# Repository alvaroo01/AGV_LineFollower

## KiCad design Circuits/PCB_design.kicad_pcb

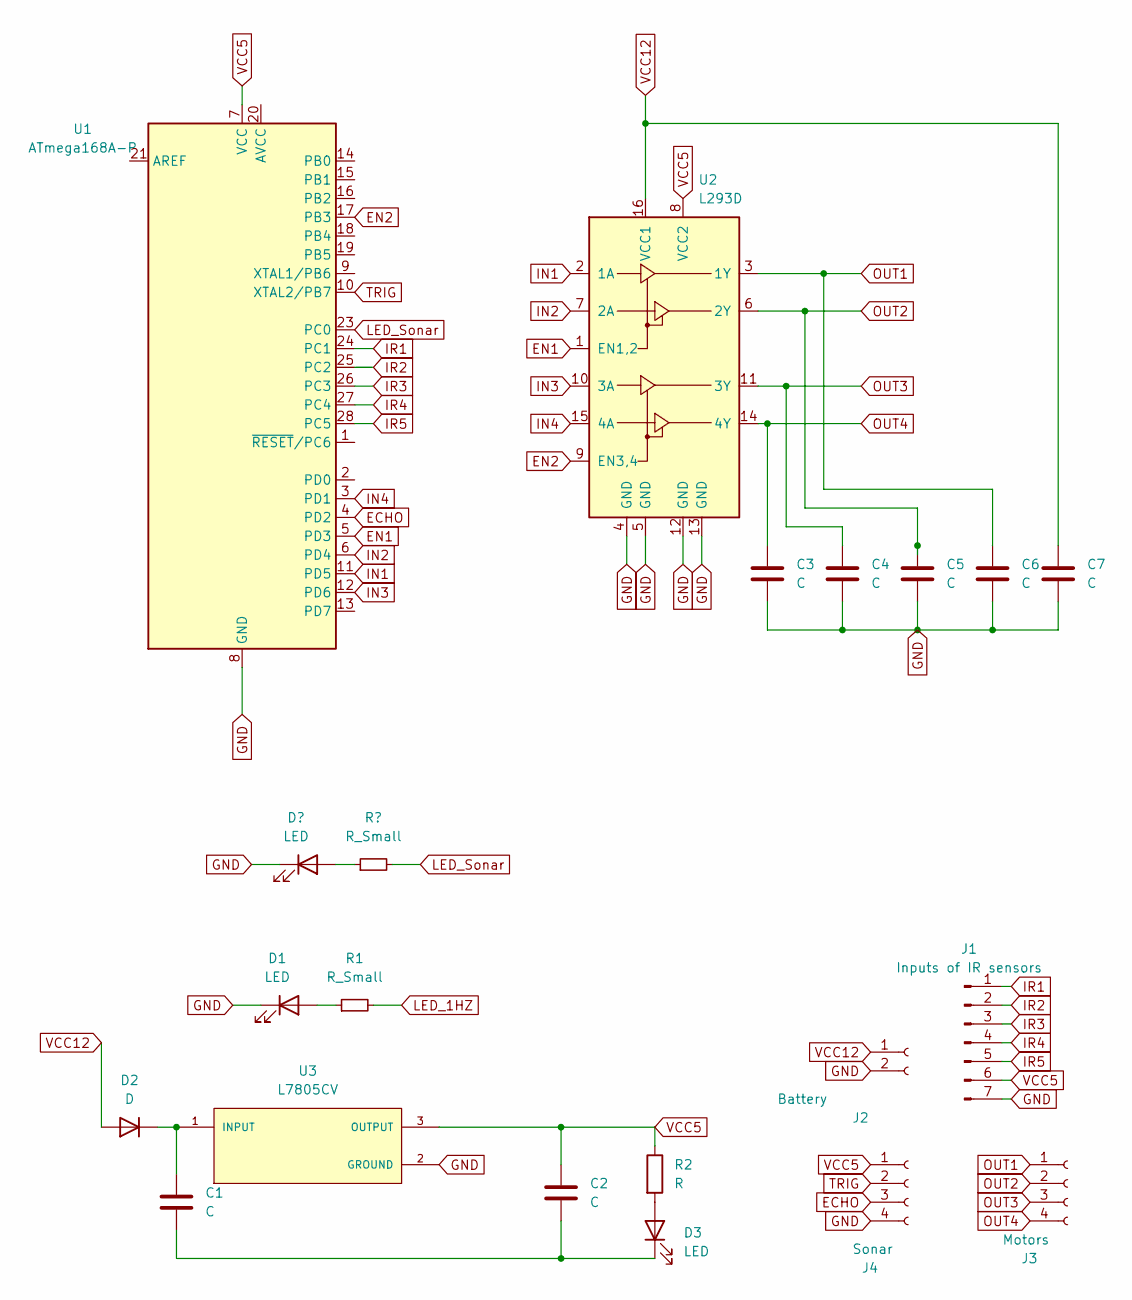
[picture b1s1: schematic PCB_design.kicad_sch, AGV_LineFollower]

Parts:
C1, C2, C3, C4, C5, C6, C7: C; C_Disc_D4.3mm_W1.9mm_P5.00mm
D1, D3: LED; LED_D3.0mm
D2: D; D_5W_P12.70mm_Horizontal
J1: Inputs of IR sensors; PinHeader_1x07_P2.54mm_Vertical
J2: Battery; PinSocket_1x02_P2.54mm_Vertical
J3: Motors; PinSocket_1x04_P2.54mm_Vertical
J4: Sonar; PinSocket_1x04_P2.54mm_Vertical
R1: R_Small; RESAD700W45L350D185
R2: R; RESAD700W45L350D185
U1: ATmega168A-P; DIP-28_W7.62mm
U2: L293D; DIP-16_W7.62mm
U3: L7805CV; TO255P1040X460X1968-3; PARTREV 36

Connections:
ECHO: J4.3, U1.4 (PD2)
EN1: U1.5 (PD3), U2.1 (EN1,2)
EN2: U1.17 (PB3), U2.9 (EN3,4)
GND: C3.2, C4.2, C5.2, C6.2, C7.2, D1.1 (K), J1.7, J2.2, J4.4, U1.8 (GND), U1.22 (GND), U2.4 (GND), U2.5 (GND), U2.12 (GND), U2.13 (GND), U3.2 (GROUND)
IN1: U1.11 (PD5), U2.2 (1A)
IN2: U1.6 (PD4), U2.7 (2A)
IN3: U1.12 (PD6), U2.10 (3A)
IN4: U1.3 (PD1), U2.15 (4A)
IR1: J1.1, U1.24 (PC1)
IR2: J1.2, U1.25 (PC2)
IR3: J1.3, U1.26 (PC3)
IR4: J1.4, U1.27 (PC4)
IR5: J1.5, U1.28 (PC5)
LED_1HZ: R1.2, U1.9 (XTAL1/PB6)
unnamed: C1.1, D2.1 (K), U3.1 (INPUT)
unnamed: C1.2, C2.2, D3.1 (K)
unnamed: D1.2 (A), R1.1
unnamed: D3.2 (A), R2.2
OUT1: C6.1, J3.1, U2.3 (1Y)
OUT2: C5.1, J3.2, U2.6 (2Y)
OUT3: C4.1, J3.3, U2.11 (3Y)
OUT4: C3.1, J3.4, U2.14 (4Y)
TRIG: J4.2, U1.10 (XTAL2/PB7)
VCC5: C2.1, J1.6, J4.1, R2.1, U1.7 (VCC), U2.8 (VCC2), U3.3 (OUTPUT)
VCC12: C7.1, D2.2 (A), J2.1, U2.16 (VCC1)

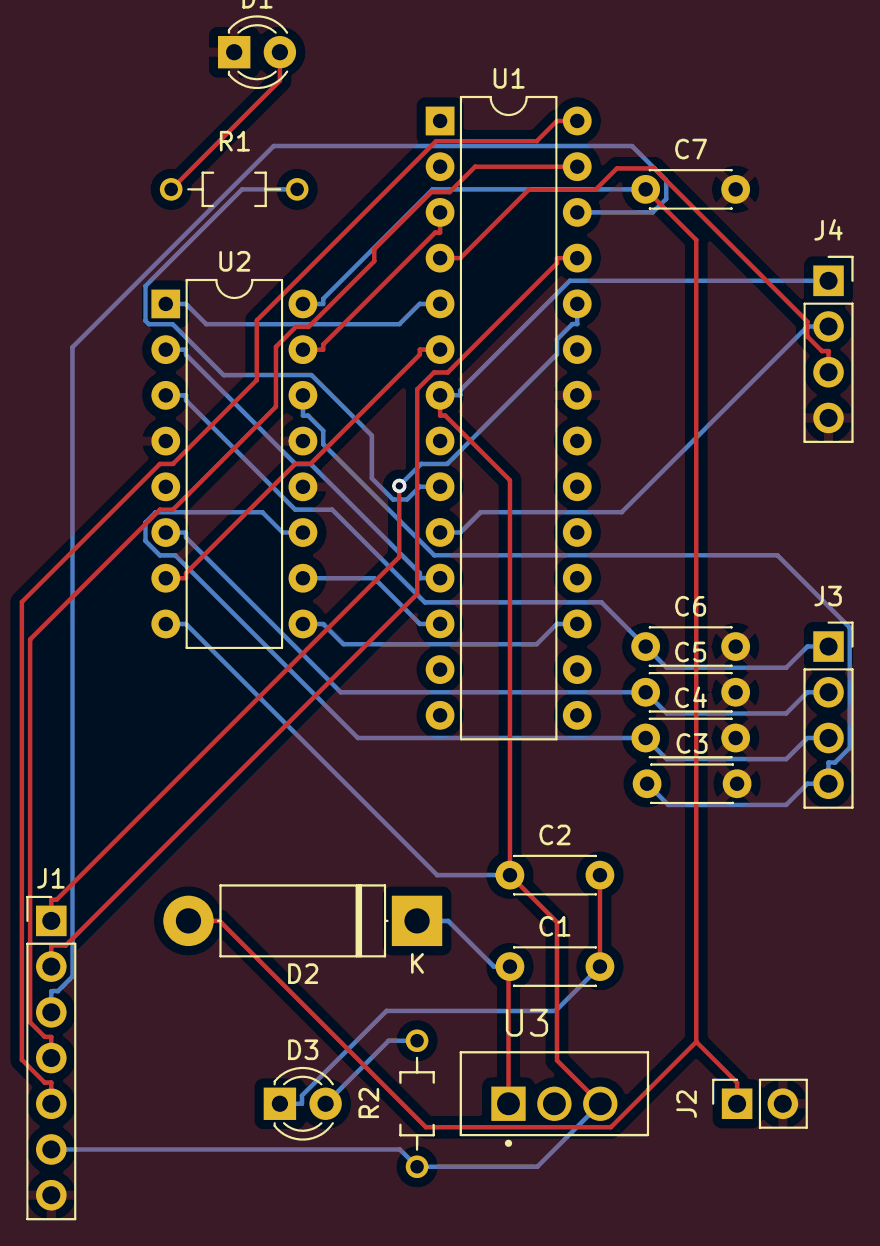
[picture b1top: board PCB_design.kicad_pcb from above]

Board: 2 copper layers, 19 parts (0 on the bottom side), 25 nets.

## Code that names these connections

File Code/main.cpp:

/*
AGV_Linefollower 
Created by:
	Álvaro Lopes-Cardoso
	Fabien Lefebvre
Date: 
	22/01/2022
*/

#include <avr/io.h>									// All the Includes necessary.
#include <stdio.h>
#define F_CPU 1000000UL
#include <util/delay.h>
#include <avr/interrupt.h>

#define motor1_velocity PD3							// Several Defines.
#define motor1_pinA PD5
#define motor1_pinB PD4
#define motor2_velocity PB3
#define motor2_pinA PD6
#define motor2_pinB PD1
#define infra_1 PC0
#define infra_2 PC1
#define infra_3 PC2
#define infra_4 PC3
#define infra_5 PC4
#define led PB2
#define delay_ 5000
#define led_1hZ PB6 
#define test_led PC0
#define Sonar_Led1 PD7
#define Sonar_Trig PB7


typedef struct										// Flag struct.
{
	unsigned char flag_ir1;
	unsigned char flag_ir2;
	unsigned char flag_ir3;
	unsigned char flag_ir4;
	unsigned char flag_ir5;
	unsigned char start_flag;
	unsigned char flag_sonar;

	
} Flags_st;

volatile Flags_st flags={0,0,0,0,0,0};

int cnt = 100;											// Counter for TC0 Interrupt.
int cm;													// Stores the distance measured by the sonar. 
int wave_time;											// Stores the time that the sonar wave took to go from the sonar to the object and back to the sonar
int sonf;												// Sonar flag for interruption. 

void init(void){
														// 0 is input and 1 is output.
														// 1 turns on Led and 0 turns off.
	DDRC = 0b00000000;									// Sets PC1, PC2, PC3, PC4, PC5 as inputs for infrareds. 
	DDRD = 0b11111010;									// Motors outputs (IN's and EN1) and Echo pin for Sonar as input and PD7 as output for Sonar Led.
	DDRB = 0b10001000;									// Motor output (EN2) output for 1Hz blinking led.
	
	PORTD = 0b00000000;									// Clear all the pins on PORTD.
	PORTB = 0b00000101;									
	PORTC = 0b00000000;									// Clears Sonar led to be off by default.
	
	//Making the 1Hz led
	
	TCCR0A = 0b00000010;								// (1<<WGM01) for CTC mode.						
	TCCR0B = 0b00000100;								// (1<<CS02) Prescaler of 256 .
	TIMSK0 = 0b00000010;								// (1<<OCIE0A) Enables Compare match A .
	OCR0A  = 19;										
	
	TCCR1A = 0b00000000;								
	EICRA = 0b00000001;									// (1<<ISC00).
	EIMSK = 0b00000001;								    // (1<<INT0).
	
	TCCR2A = 0b10100011;							    // Clear OC2B and OC2A on compare match and define operation mode as Fast PWM.
	TCCR2B = 0b00000101;								// (1<<CS22) (1<<CS20) Prescaler of 128.
	OCR2B=0;											// Left motor pwm.
	OCR2A=0;											// Right motor pwm.
	
	sei();												// Activates all interruptions.
}


void sonar(void)
{
	PORTB|=(1<<Sonar_Trig);								// Trig pin in set on HIGH.
	_delay_us(10);										// Waits for 10us. 
	PORTB &=~(1<<Sonar_Trig);							// Trig pin in set on LOW.
	cm = (wave_time/58);								// The distance is calculated.		

	if(cm<=25)											// If the distance is less than 25cm then...
	{
		flags.flag_sonar = 1;							// Sonar flag goes to 1.
		PORTD |= (1<<Sonar_Led1);						// Sonar led turns on
		}else{
		PORTD &= ~(1<<Sonar_Led1);						// Sonar led turns off
		flags.flag_sonar = 0;							// Sonar flag goes to 0.
	}
}




void forward (int vel){									// Car goes forward.
	
	OCR2B = vel;										// Sets the speed of both motors
	OCR2A = vel;
	//M1
	PORTD |= (1<<motor1_pinA);							// Current flows in a certain direction allowing both motors to be in the forward direction
	PORTD &= ~(1<<motor1_pinB);
	//M2
	PORTD |= (1<<motor2_pinA);	
	PORTD &= ~(1<<motor2_pinB);
	
}

void backwards (int vel){								// Car goes backwards.
	//M1
	OCR2B = vel;										// Sets the speed of both motors.
	OCR2A = vel;
	PORTD &= ~(1<<motor1_pinA);							// Current flows in a certain direction allowing both motors to be in the backwards direction.
	PORTD |= (1<<motor1_pinB);							
	//M2
	PORTD &= ~(1<<motor2_pinA);
	PORTD |= (1<<motor2_pinB);
	
}

void stop (){											// Car stops.
	//M1
	OCR2B = 0;											// Sets the speed of both motors at 0.
	OCR2A = 0;
	PORTD &= ~(1<<motor1_pinA);							// No current goes to the motors.
	PORTD &= ~(1<<motor1_pinB);
	//M2
	PORTD &= ~(1<<motor2_pinA);
	PORTD &= ~(1<<motor2_pinB);
}

void left (int vel1, int vel2){							// Car goes right (The name of the function relates to the motor thats rotating, so if the left motor is rotating and the right one isn't the car goes right).
	//right motor is A	
	//left motor is B
	OCR2B = vel1;										// Sets the speed of both motors.
	OCR2A = vel2;
	PORTD |= (1<<motor1_pinA);							// Current flows in a certain direction allowing both motors to be in the forward direction.
	PORTD &= ~(1<<motor1_pinB);
}

void right (int vel1, int vel2){						// Car goes left (The name of the function relates to the motor thats rotating, so if the right motor is rotating and the left one isn't the car goes left).
	//right motor is A
	//left motor is B
	OCR2B = vel2;										// Sets the speed of both motors.
	OCR2A = vel1;
	PORTD |= (1<<motor1_pinA);							// Current flows in a certain direction allowing both motors to be in the forward direction.
	PORTD &= ~(1<<motor1_pinB);	
}
	
void start (int start_vel){								// Function that determines when the car starts.
	if ((PINC | 0b11000001) == 0b11000001)				// If every IR Sensor is detecting black then the car starts.	
		{
		forward(start_vel);								// The car starts going forward.
		flags.start_flag = 1;							// Changes the start_flag to 1.
		}
		}

void ir_sensors(	int start_vel, int low_speed){			// Function that determines when the car changes direction or stops when it has already started.
	sonar();												// Runs the sonar() funciton.
	if ((PINC | 0b11111101) == 0b11111101){					// If IR1 is detecting black...
		while(!((PINC | 0b11110111) == 0b11110111)){		// While IR3 isn't detecting black...
			right(start_vel,0);								// Car goes left.
		}		
		
		} else if ((PINC | 0b11011111) == 0b11011111){		// If IR5 is detecting black...
		while(!((PINC | 0b11110111) == 0b11110111)){		// While IR3 isn't detecting black...
			left(start_vel,0);								// Car goes right.
		}
		
		} else if ((PINC | 0b11101111) == 0b11101111){		// If IR4 is detecting black...
			left(start_vel,0);								// Car goes right.
		
		} else if ((PINC | 0b11111011) == 0b11111011){		// If IR2 is detecting black...
			right(start_vel,0);								// Car goes left.
			
		} else if (flags.flag_sonar==1){					// If Sonar detects an object...
			while(!(flags.flag_sonar==0)) {					// While it doesn't stop detecting....
				stop();										// Car stops.
				sonar();									// Reads the sonar again.
			}
			forward(80);									// Car goes forward with higher speed to be able to have enought startign torque.
		
		} else forward(start_vel);							// Car goes forward normally.
	
}


int main(void)												// Main function
{	
	init();													// Runs the init() function.
	int velocity =	35;										// Sets main velocity of the car. 	
	while (1)												// While loop.
	{
		flags.start_flag = 0;								// Sets start flag to 0. Just a precaution. 
		sonar();											// Runs the sonar() function.
		if(flags.flag_sonar == 0) {							// If sonar isn't detecting anything...
		start(velocity);									// Starts the car.
		} else stop();										// If the above conditions weren't met then the car stops.
		while(flags.start_flag == 1){						// If the car has started...
			ir_sensors(velocity, 25);						// Run the function ir_sensors on a loop. 
			}
		}
	}


ISR(TIMER0_COMPA_vect)										// Interruption generated by Timer0.
{
	cnt--;													// Decrements the counter.
	if (cnt==0){											// If the counter has reached 0 then...
		PORTB ^= (1<<led_1hZ);								// Swap the state of the bit (0 to 1 or 1 to 0).
		cnt = 100;											// Return counter to 100. 
	}
}

ISR(INT0_vect)												// Interruption for the sonar.	
{
	if(sonf == 0)											// The sonf is a flag that makes sure that the Low-High state change initiates the timer and the High-Low state change stops the timer.
	{
		TCCR1B |= 1<<CS10;									// By giving it a prescaler we initiate the timer.			
		TCNT1 = 0;											// We set TCNT1 to zero in order to clear it to start the count.
		sonf = 1;											
	}
	else
	{
		wave_time = TCNT1;									// Retrieving how much time passed.
		TCCR1B = 0;											// Turning off the Timer.
		sonf = 0;
	}
}

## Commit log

2022-01-22 i think last commit
2022-01-22 Circuits Update
2022-01-22 Update
    Circuit Squeme and Datasheets
2022-01-26 Video and small code update
